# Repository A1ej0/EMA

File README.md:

<div align="center">

</div>  

# <div align="center">EMA - Estación de Monitoreo Automático 🍃</div>  

<div align="right">

</div>  

-  De bajo costo💸  

- Enfoque comunitario 🙆🧑‍🎓🧑‍🌾🧑‍🍳🧑‍🚒  

- De alta tecnologia 🚀🛸  

<br/>  

## Que es?  
EMA nace con el objetivo de brindar una alternativa con un sentido social y un enfoque comunitario a dispositivos tecnológicos de alto coste y complejidad, brindando la oportunidad a la comunidad de participar en temas relacionados a la medición de variables medioambientales para el monitoreo de diferentes factores como lluvias, movimientos del suelo, crecimiento de los ríos y calidad de agua. 🌋🏔️🏞️

Todo esto a muy bajo coste y una construcción modular, con partes de muy fácil obtención para promover la participación de todo el mundo 
🌎  

<br/>  

## Que incluye?  
<div align="center">  

</div>  

El proyecto EMA esta diseñado con un enfoque de codigo abierto y software libre, es por esto que se usaron lenguajes de programacion y aplicativos con este enfoque, para el modulo principal que incluye la placa principal del proyecto (ESP32), se uso micropython, para los sensores externos que requieren un microcontrolador para ser interpretados se uso C++ como codigo de programacion, para la interface web, se hizo uso de Node-red, proyecto de codigo abierto creado por IBM y finalmente Mosquitto como broker de MQTT  

<br/>  

## Características  
- ### Conexión ✨  

📶 Bluetooth, Diseñado para lectura, ajuste y extracción de información desde dispositivos móviles

🥝Wifi, Diseñado para el envió de lecturas de los sensores al servidor del proyecto

📱GPRS, Diseñado para el envió de lectura de sensores mediante una red móvil en caso de ausencia de wifi

📝MicroSD, diseñada para almacenar de forma local lectura de sensores en caso de ausencia de cualquier lectura y como forma de llevar registros

- ### Módulos 🧩  

Los módulos son los sensores que es capaz de leer EMA  

⛈️ Pluviómetro, modulo diseñado para leer los niveles de lluvia en la zona

📏 Distancia, modulo diseñado con ultrasonido para medir distancias de niveles de ríos o similares

🏜️ Temperatura, Modulo diseñado para medir la temperatura medio ambiental

🚄 Aceleración, Modulo diseñado para medir el movimiento de los suelos, montañas, etc

⌛ Reloj, Modulo diseñado para llevar un registro de tiempo del momento de toma de lecturas

💧Calidad de agua, Modulo diseñado para medir el nivel de contaminación de ríos o cuerpos de agua  

- ### Proyección 🚀✨  

Se espera para el futuro la integración de módulos adicionales para lecturas de variables medioambientales diferentes con una variedad mas amplia de sensores, también se pretende el diseño y construcción de un sistema de programación remoto por medio del cual los usuarios podrán cargar el programa en la placa de desarrollo sin requerir ningún programa mas allá de un navegador web 💻  

<br />

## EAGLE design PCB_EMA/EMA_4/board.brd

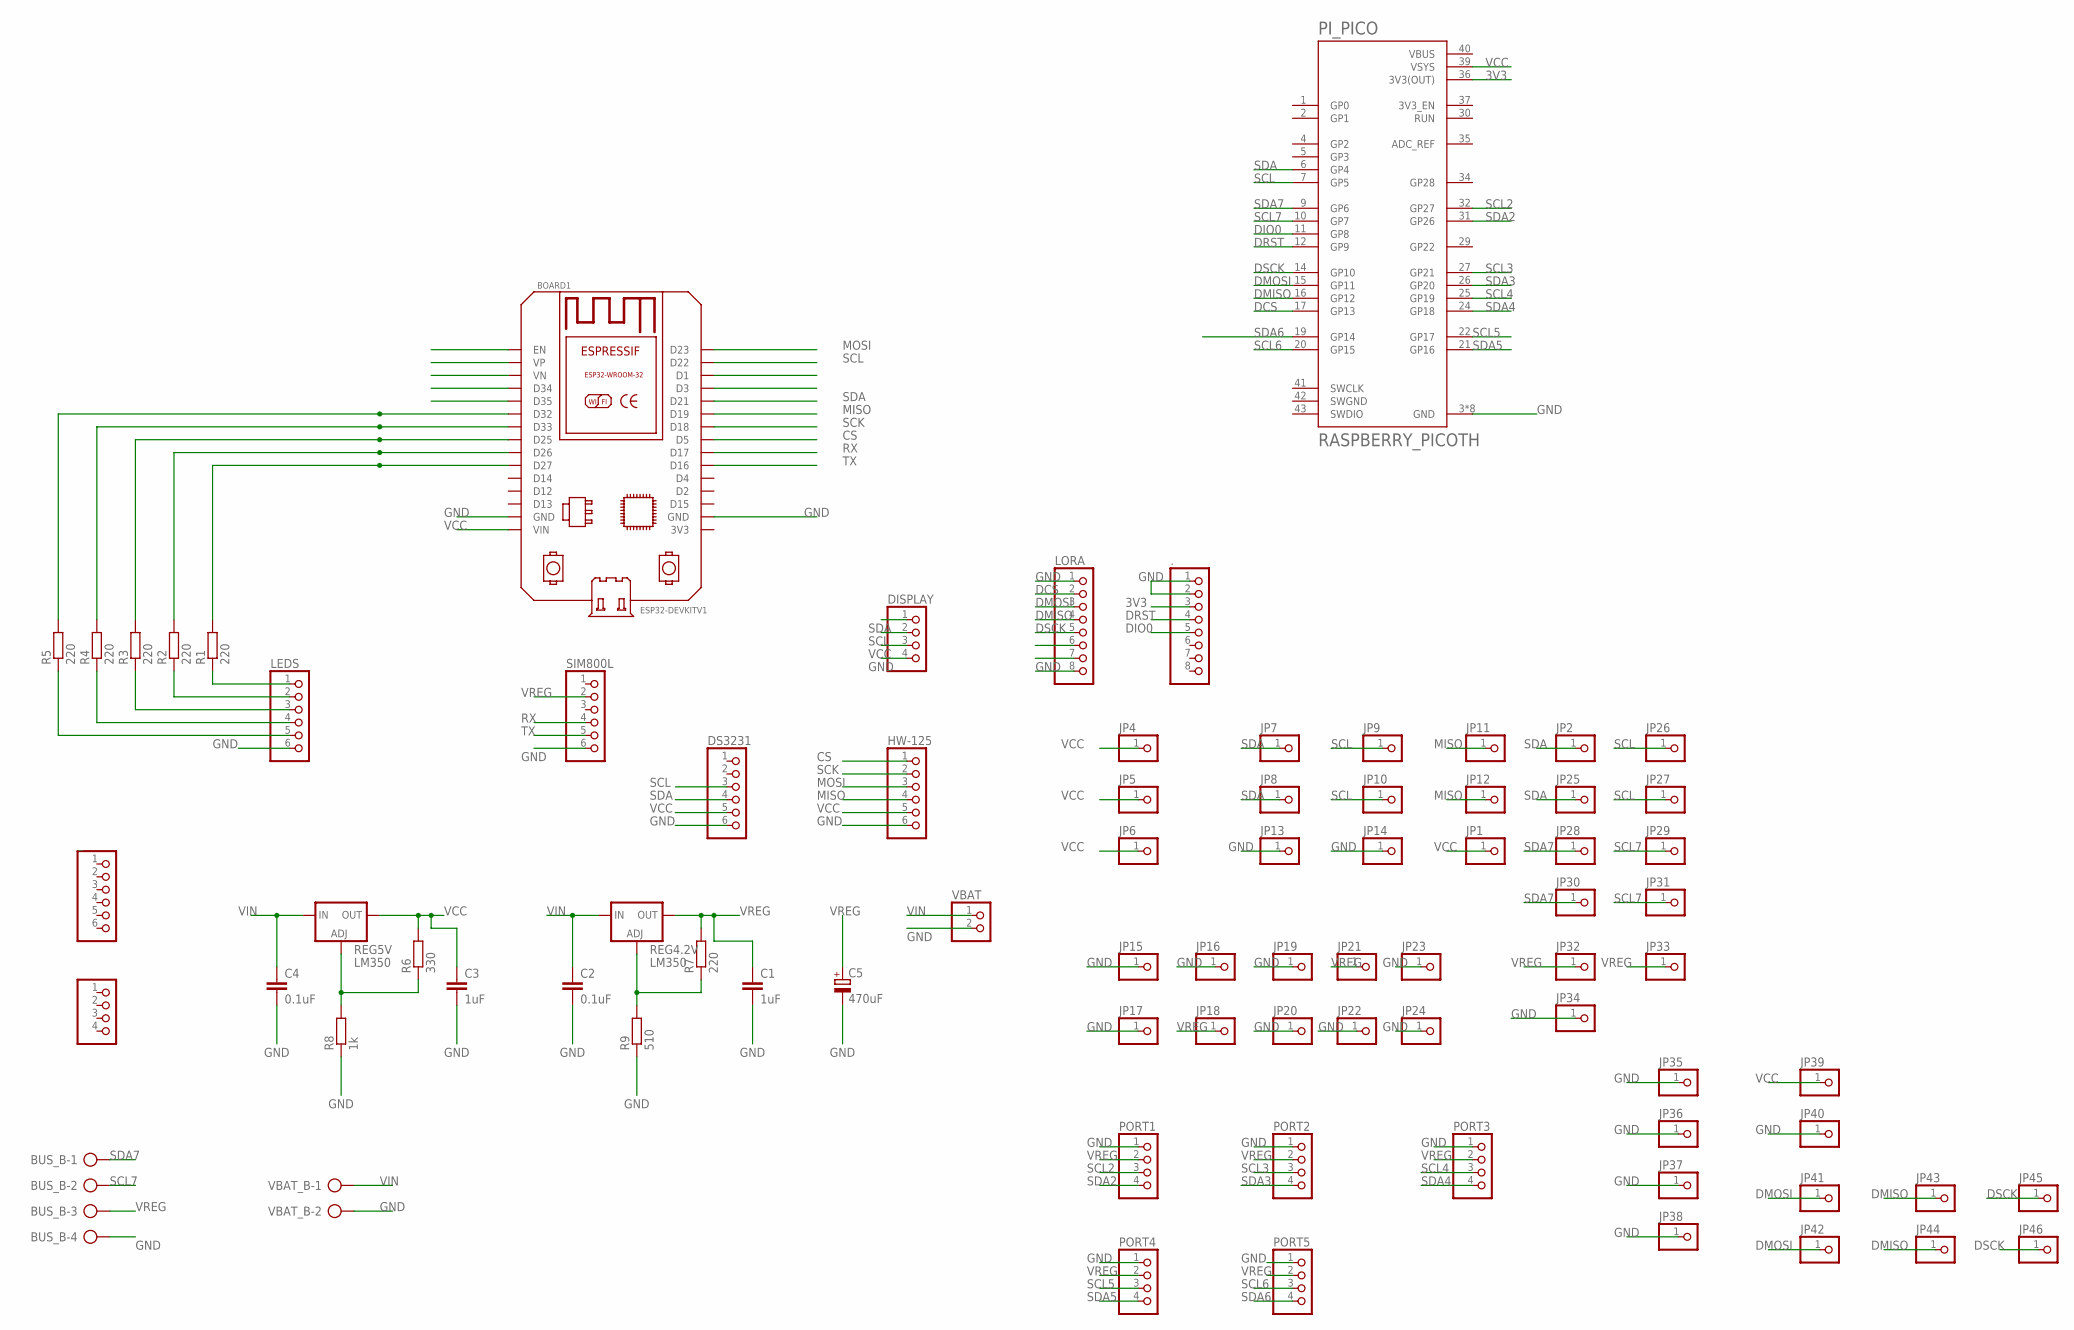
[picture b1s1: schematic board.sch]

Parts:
.: PINHD-1X8; 1X08
BOARD1: ESP32DEVKITV1; ESP32-DEVKITV1
BUS_B: AK500/4-H
C1, C3: 1uF; C2.5-2
C2, C4: 0.1uF; C2.5-2
C5: 470uF; E3,5-8
DISPLAY: PINHD-1X4; 1X04
DS3231: PINHD-1X6; 1X06
HW-125: PINHD-1X6; 1X06
JP1, JP2, JP4, JP5, JP6, JP7, JP8, JP9, JP10, JP11, JP12, JP13, JP14, JP15, JP16, JP17, JP18, JP19, JP20, JP21, JP22, JP23, JP24, JP25, JP26, JP27, JP28, JP29, JP30, JP31, JP32, JP33, JP34, JP35, JP36, JP37, JP38, JP39, JP40, JP41, JP42, JP43, JP44, JP45, JP46: PINHD-1X1; 1X01
JP3: PINHD-1X4; 1X04
LEDS: PINHD-1X6; 1X06
LORA: PINHD-1X8; 1X08
PI_PICO: RASPBERRY_PICOTH; PICO-PKG-TH
PORT1, PORT2, PORT3, PORT4, PORT5: PINHD-1X4; 1X04
R1, R2, R3, R4, R5: 220; R1206
R6: 330; 0204/7
R7: 220; 0204/7
R8: 1k; 0204/7
R9: 510; 0204/7
REG4.2V, REG5V: LM350; 317TS
SIM800L: PINHD-1X6; 1X06
VBAT: PINHD-1X2; 1X02
VBAT_B: AK500/2-H
_: PINHD-1X6; 1X06

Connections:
3V3: ..3, PI_PICO.36 (3V3(OUT))
CS: BOARD1.D5, HW-125.1
DCS: LORA.2, PI_PICO.17 (GP13)
DIO0: ..5, PI_PICO.11 (GP8)
DMISO: JP43.1, JP44.1, LORA.4, PI_PICO.16 (GP12)
DMOSI: JP41.1, JP42.1, LORA.3, PI_PICO.15 (GP11)
DRST: ..4, PI_PICO.12 (GP9)
DSCK: JP45.1, JP46.1, LORA.5, PI_PICO.14 (GP10)
GND: ..1, ..2, BOARD1.GND, BOARD1.GND@1 (GND), BUS_B.4, C1.2, C2.2, C3.2, C4.2, C5.-, DISPLAY.4, DS3231.6, HW-125.6, JP13.1, JP14.1, JP15.1, JP16.1, JP17.1, JP19.1, JP20.1, JP22.1, JP23.1, JP24.1, JP34.1, JP35.1, JP36.1, JP37.1, JP38.1, JP40.1, LEDS.6, LORA.1, LORA.8, PI_PICO.3 (GND), PI_PICO.8 (GND), PI_PICO.13 (GND), PI_PICO.18 (GND), PI_PICO.23 (GND), PI_PICO.28 (GND), PI_PICO.33 (GND), PI_PICO.38 (GND), PORT1.1, PORT2.1, PORT3.1, PORT4.1, PORT5.1, R8.1, R9.1, SIM800L.6, VBAT.2, VBAT_B.2
MISO: BOARD1.D19, HW-125.4, JP11.1, JP12.1
MOSI: BOARD1.D23, HW-125.3
unnamed: BOARD1.D32, R5.2
unnamed: BOARD1.D33, R4.2
unnamed: BOARD1.D25, R3.2
unnamed: BOARD1.D26, R2.2
unnamed: BOARD1.D27, R1.2
unnamed: LEDS.1, R1.1
unnamed: LEDS.2, R2.1
unnamed: LEDS.3, R3.1
unnamed: LEDS.4, R4.1
unnamed: LEDS.5, R5.1
unnamed: R6.1, R8.2, REG5V.1 (ADJ)
unnamed: R7.1, R9.2, REG4.2V.1 (ADJ)
RX: BOARD1.D17, SIM800L.4
SCK: BOARD1.D18, HW-125.2
SCL: BOARD1.D22, DISPLAY.2, DS3231.3, JP9.1, JP10.1, JP26.1, JP27.1, PI_PICO.7 (GP5)
SCL2: PI_PICO.32 (GP27), PORT1.3
SCL3: PI_PICO.27 (GP21), PORT2.3
SCL4: PI_PICO.25 (GP19), PORT3.3
SCL5: PI_PICO.22 (GP17), PORT4.3
SCL6: PI_PICO.20 (GP15), PORT5.3
SCL7: BUS_B.2, JP29.1, JP31.1, PI_PICO.10 (GP7)
SDA: BOARD1.D21, DISPLAY.1, DS3231.4, JP2.1, JP7.1, JP8.1, JP25.1, PI_PICO.6 (GP4)
SDA2: PI_PICO.31 (GP26), PORT1.4
SDA3: PI_PICO.26 (GP20), PORT2.4
SDA4: PI_PICO.24 (GP18), PORT3.4
SDA5: PI_PICO.21 (GP16), PORT4.4
SDA6: PI_PICO.19 (GP14), PORT5.4
SDA7: BUS_B.1, JP28.1, JP30.1, PI_PICO.9 (GP6)
SWGND: PI_PICO.42 (SWGND)
TX: BOARD1.D16, SIM800L.5
VBUS: PI_PICO.40 (VBUS)
VCC: BOARD1.VIN, C3.1, DISPLAY.3, DS3231.5, HW-125.5, JP1.1, JP4.1, JP5.1, JP6.1, JP39.1, PI_PICO.39 (VSYS), R6.2, REG5V.2 (OUT)
VIN: C2.1, C4.1, REG4.2V.3 (IN), REG5V.3 (IN), VBAT.1, VBAT_B.1
VREG: BUS_B.3, C1.1, C5.+, JP18.1, JP21.1, JP32.1, JP33.1, PORT1.2, PORT2.2, PORT3.2, PORT4.2, PORT5.2, R7.2, REG4.2V.2 (OUT), SIM800L.2

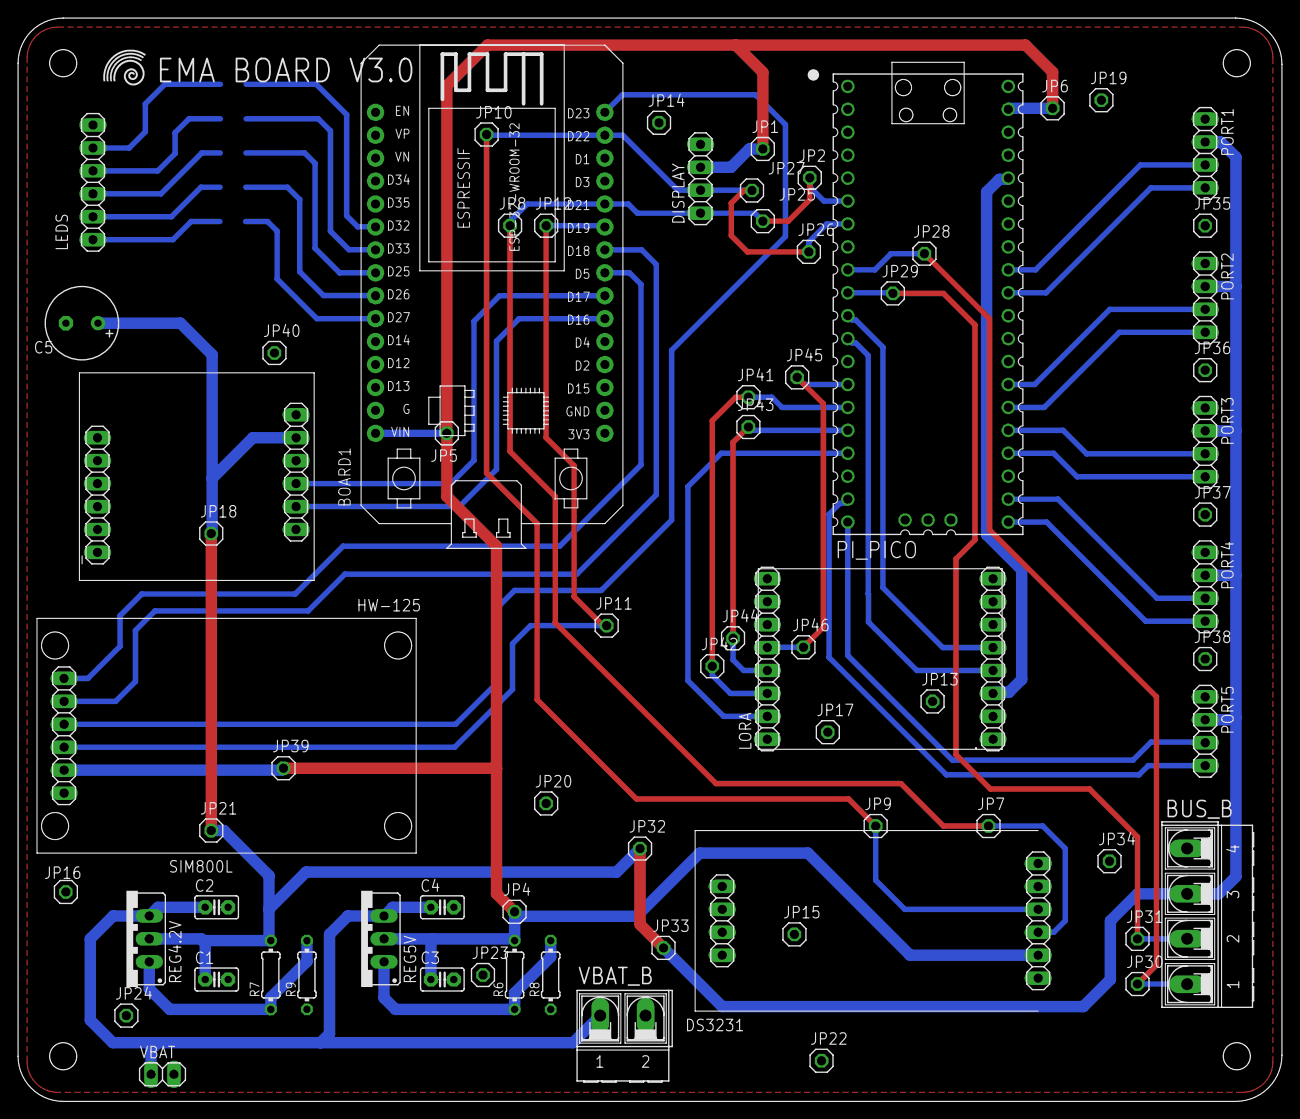
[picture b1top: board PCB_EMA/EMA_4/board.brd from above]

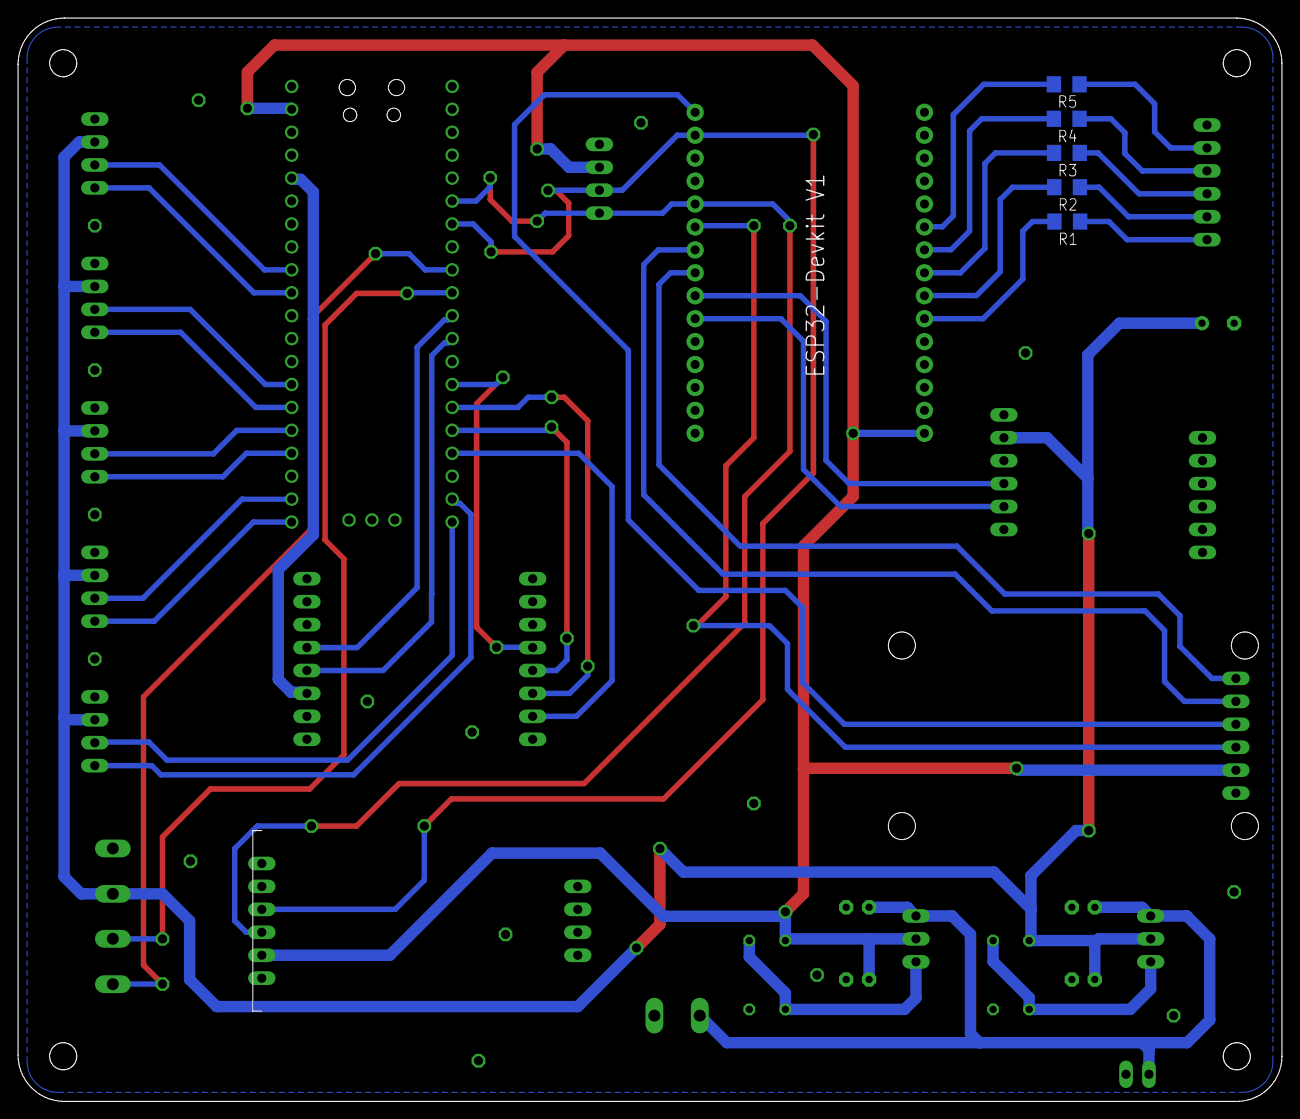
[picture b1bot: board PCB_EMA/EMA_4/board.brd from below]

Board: 2 copper layers, 140.0 x 120.0 mm, 80 parts (5 on the bottom side), 43 nets.

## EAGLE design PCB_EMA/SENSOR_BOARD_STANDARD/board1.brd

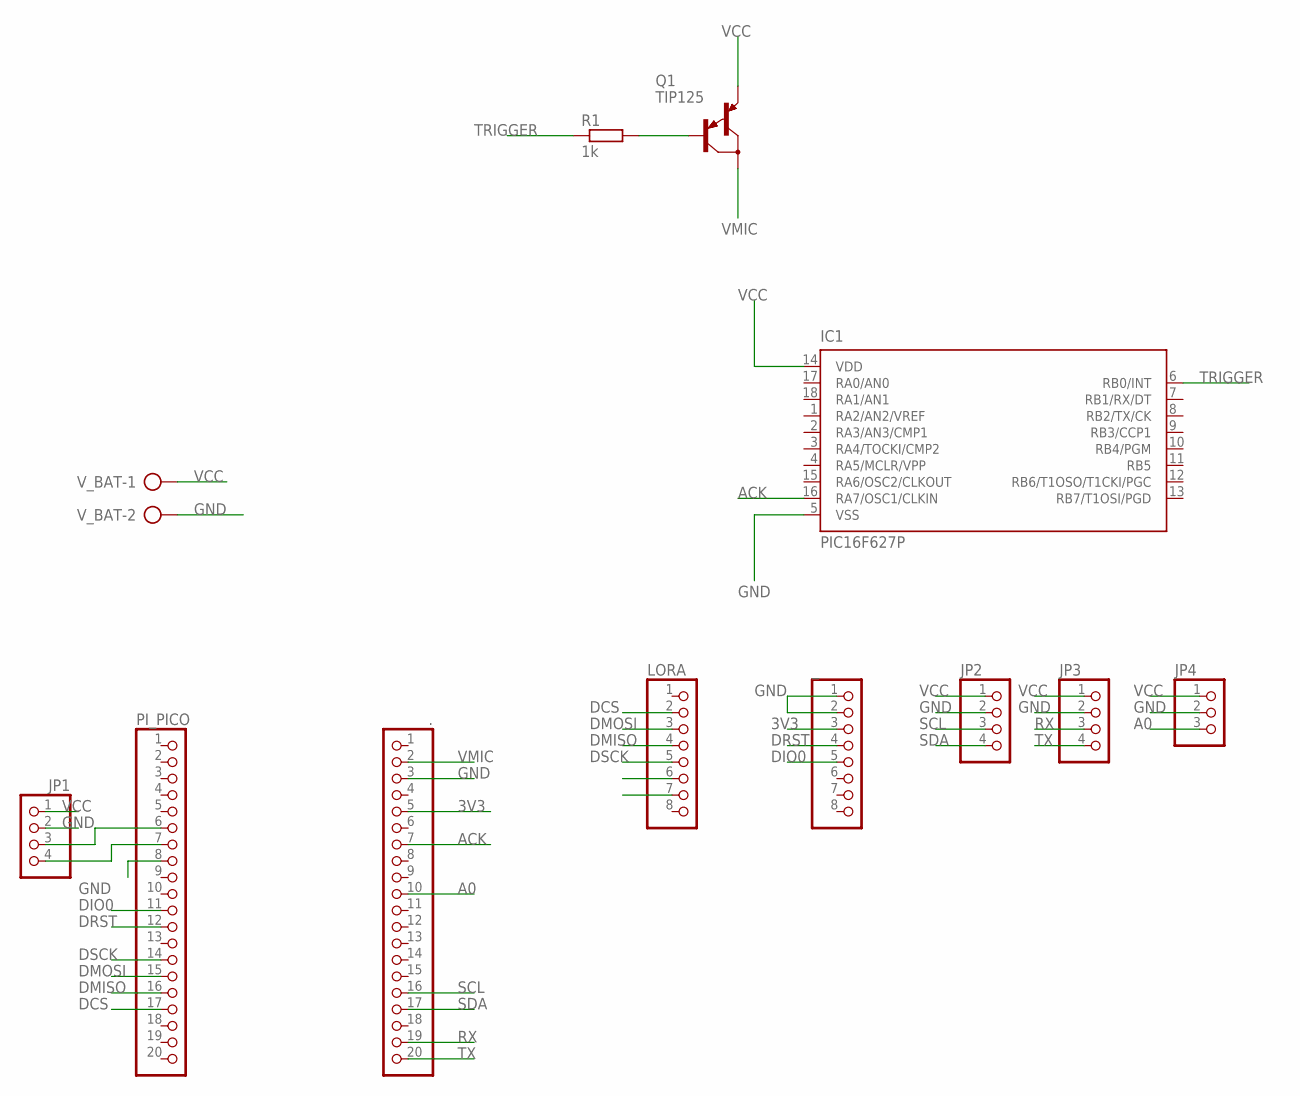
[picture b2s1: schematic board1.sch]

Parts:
.: PINHD-1X20; 1X20
IC1: PIC16F627P; DIL18
JP1, JP2, JP3: PINHD-1X4; 1X04
JP4: PINHD-1X3; 1X03
LORA: PINHD-1X8; 1X08
PI_PICO: PINHD-1X20; 1X20
Q1: TIP125; TO220
R1: 1k; 0411/15
V_BAT: AK500/2-H
_: PINHD-1X8; 1X08

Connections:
3V3: ..5, _.3
A0: ..10, JP4.3
ACK: ..7, IC1.16 (RA7/OSC1/CLKIN)
DCS: LORA.2, PI_PICO.17
DIO0: PI_PICO.11, _.5
DMISO: LORA.4, PI_PICO.16
DMOSI: LORA.3, PI_PICO.15
DRST: PI_PICO.12, _.4
DSCK: LORA.5, PI_PICO.14
GND: ..3, IC1.5 (VSS), JP1.2, JP2.2, JP3.2, JP4.2, PI_PICO.8, V_BAT.2, _.1, _.2
unnamed: JP1.4, PI_PICO.7
unnamed: JP1.3, PI_PICO.6
unnamed: Q1.1 (B), R1.2
RX: ..19, JP3.3
SCL: ..16, JP2.3
SDA: ..17, JP2.4
TRIGGER: IC1.6 (RB0/INT), R1.1
TX: ..20, JP3.4
VCC: IC1.14 (VDD), JP1.1, JP2.1, JP3.1, JP4.1, Q1.3 (E), V_BAT.1
VMIC: ..2, Q1.2 (C)

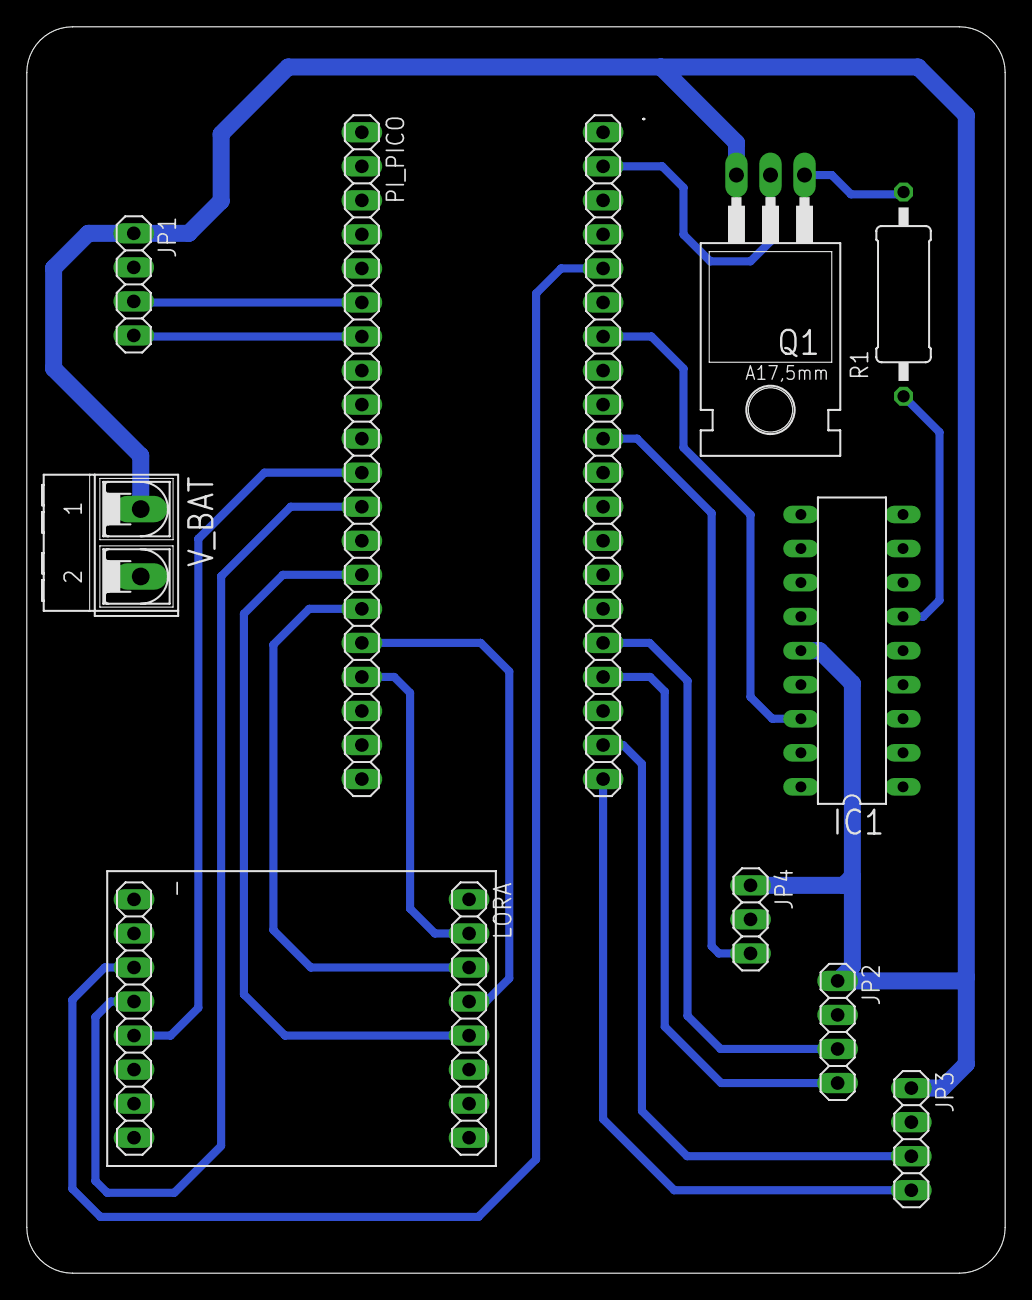
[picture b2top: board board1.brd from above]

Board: 2 copper layers, 73.0 x 93.0 mm, 12 parts (0 on the bottom side), 20 nets.

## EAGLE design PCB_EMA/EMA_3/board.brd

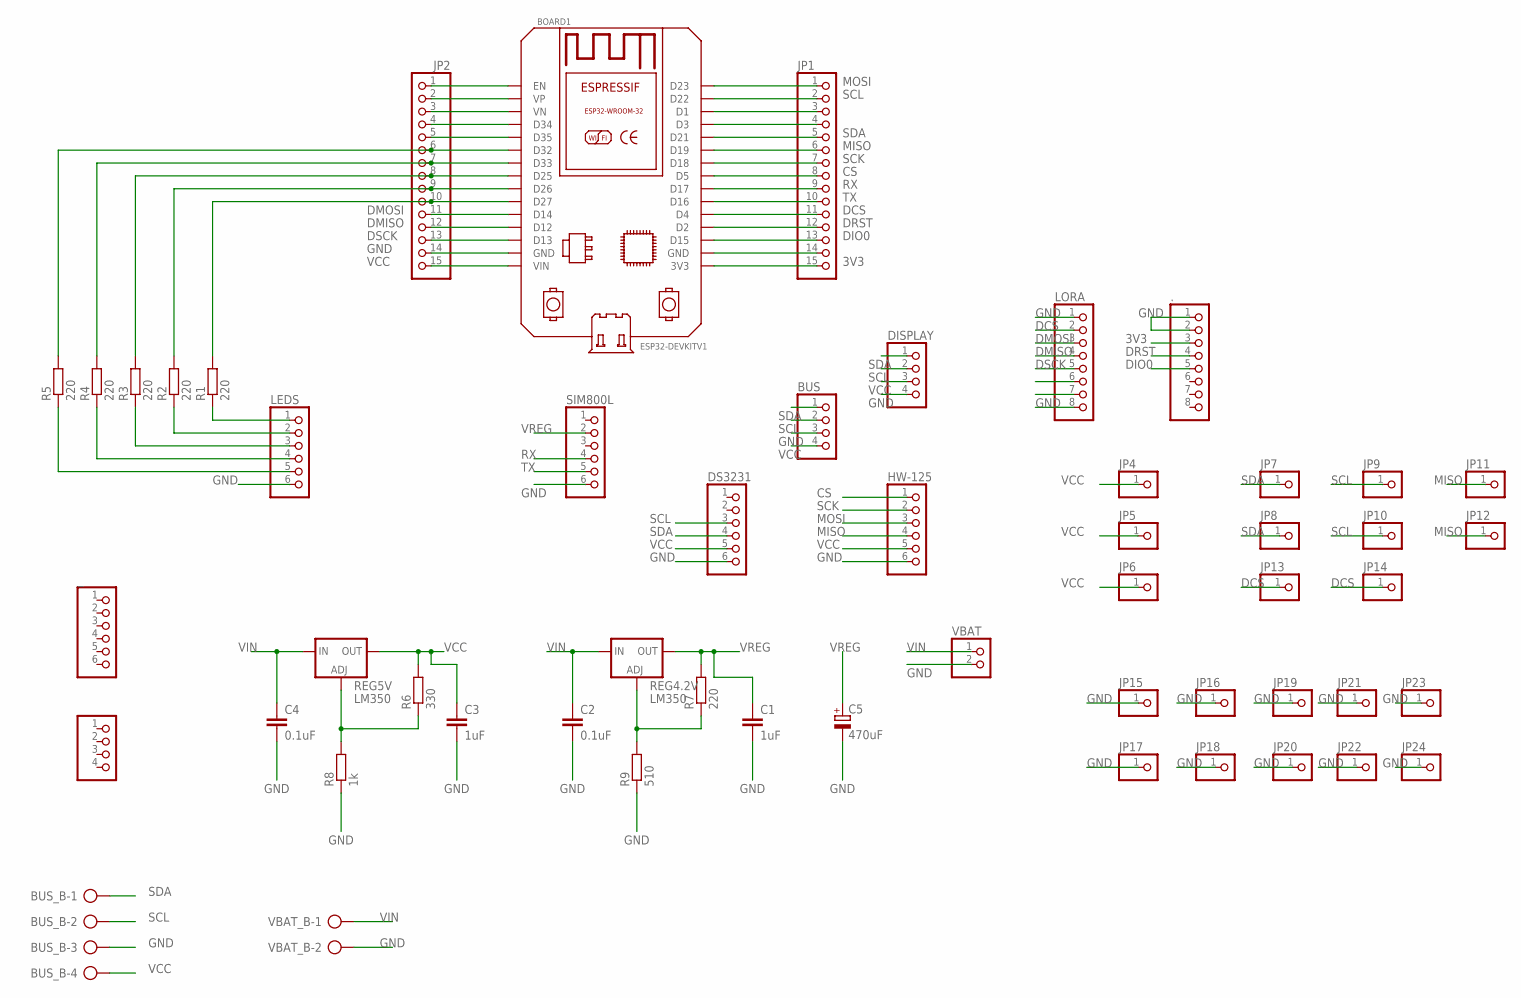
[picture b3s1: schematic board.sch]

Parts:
.: PINHD-1X8; 1X08
BOARD1: ESP32DEVKITV1; ESP32-DEVKITV1
BUS: PINHD-1X4; 1X04
BUS_B: AK500/4-H
C1, C3: 1uF; C2.5-2
C2, C4: 0.1uF; C2.5-2
C5: 470uF; E3,5-8
DISPLAY: PINHD-1X4; 1X04
DS3231: PINHD-1X6; 1X06
HW-125: PINHD-1X6; 1X06
JP1, JP2: PINHD-1X15; 1X15
JP3: PINHD-1X4; 1X04
JP4, JP5, JP6, JP7, JP8, JP9, JP10, JP11, JP12, JP13, JP14, JP15, JP16, JP17, JP18, JP19, JP20, JP21, JP22, JP23, JP24: PINHD-1X1; 1X01
LEDS: PINHD-1X6; 1X06
LORA: PINHD-1X8; 1X08
R1, R2, R3, R4, R5: 220; R1206
R6: 330; 0204/7
R7: 220; 0204/7
R8: 1k; 0204/7
R9: 510; 0204/7
REG4.2V, REG5V: LM350; 317TS
SIM800L: PINHD-1X6; 1X06
VBAT: PINHD-1X2; 1X02
VBAT_B: AK500/2-H
_: PINHD-1X6; 1X06

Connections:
3V3: ..3, BOARD1.3V3, JP1.15
CS: BOARD1.D5, HW-125.1, JP1.8
DCS: BOARD1.D4, JP1.11, JP13.1, JP14.1, LORA.2
DIO0: ..5, BOARD1.D15, JP1.13
DMISO: BOARD1.D12, JP2.12, LORA.4
DMOSI: BOARD1.D14, JP2.11, LORA.3
DRST: ..4, BOARD1.D2, JP1.12
DSCK: BOARD1.D13, JP2.13, LORA.5
GND: ..1, ..2, BOARD1.GND, BUS.3, BUS_B.3, C1.2, C2.2, C3.2, C4.2, C5.-, DISPLAY.4, DS3231.6, HW-125.6, JP2.14, JP15.1, JP16.1, JP17.1, JP18.1, JP19.1, JP20.1, JP21.1, JP22.1, JP23.1, JP24.1, LEDS.6, LORA.1, LORA.8, R8.1, R9.1, SIM800L.6, VBAT.2, VBAT_B.2
MISO: BOARD1.D19, HW-125.4, JP1.6, JP11.1, JP12.1
MOSI: BOARD1.D23, HW-125.3, JP1.1
unnamed: BOARD1.EN, JP2.1
unnamed: BOARD1.VP, JP2.2
unnamed: BOARD1.VN, JP2.3
unnamed: BOARD1.D34, JP2.4
unnamed: BOARD1.D35, JP2.5
unnamed: BOARD1.D32, JP2.6, R5.2
unnamed: BOARD1.D33, JP2.7, R4.2
unnamed: BOARD1.D25, JP2.8, R3.2
unnamed: BOARD1.D26, JP2.9, R2.2
unnamed: BOARD1.D27, JP2.10, R1.2
unnamed: LEDS.1, R1.1
unnamed: LEDS.2, R2.1
unnamed: LEDS.3, R3.1
unnamed: LEDS.4, R4.1
unnamed: LEDS.5, R5.1
unnamed: BOARD1.D1, JP1.3
unnamed: BOARD1.D3, JP1.4
unnamed: BOARD1.GND@1 (GND), JP1.14
unnamed: R6.1, R8.2, REG5V.1 (ADJ)
unnamed: R7.1, R9.2, REG4.2V.1 (ADJ)
RX: BOARD1.D17, JP1.9, SIM800L.4
SCK: BOARD1.D18, HW-125.2, JP1.7
SCL: BOARD1.D22, BUS.2, BUS_B.2, DISPLAY.2, DS3231.3, JP1.2, JP9.1, JP10.1
SDA: BOARD1.D21, BUS.1, BUS_B.1, DISPLAY.1, DS3231.4, JP1.5, JP7.1, JP8.1
TX: BOARD1.D16, JP1.10, SIM800L.5
VCC: BOARD1.VIN, BUS.4, BUS_B.4, C3.1, DISPLAY.3, DS3231.5, HW-125.5, JP2.15, JP4.1, JP5.1, JP6.1, R6.2, REG5V.2 (OUT)
VIN: C2.1, C4.1, REG4.2V.3 (IN), REG5V.3 (IN), VBAT.1, VBAT_B.1
VREG: C1.1, C5.+, R7.2, REG4.2V.2 (OUT), SIM800L.2

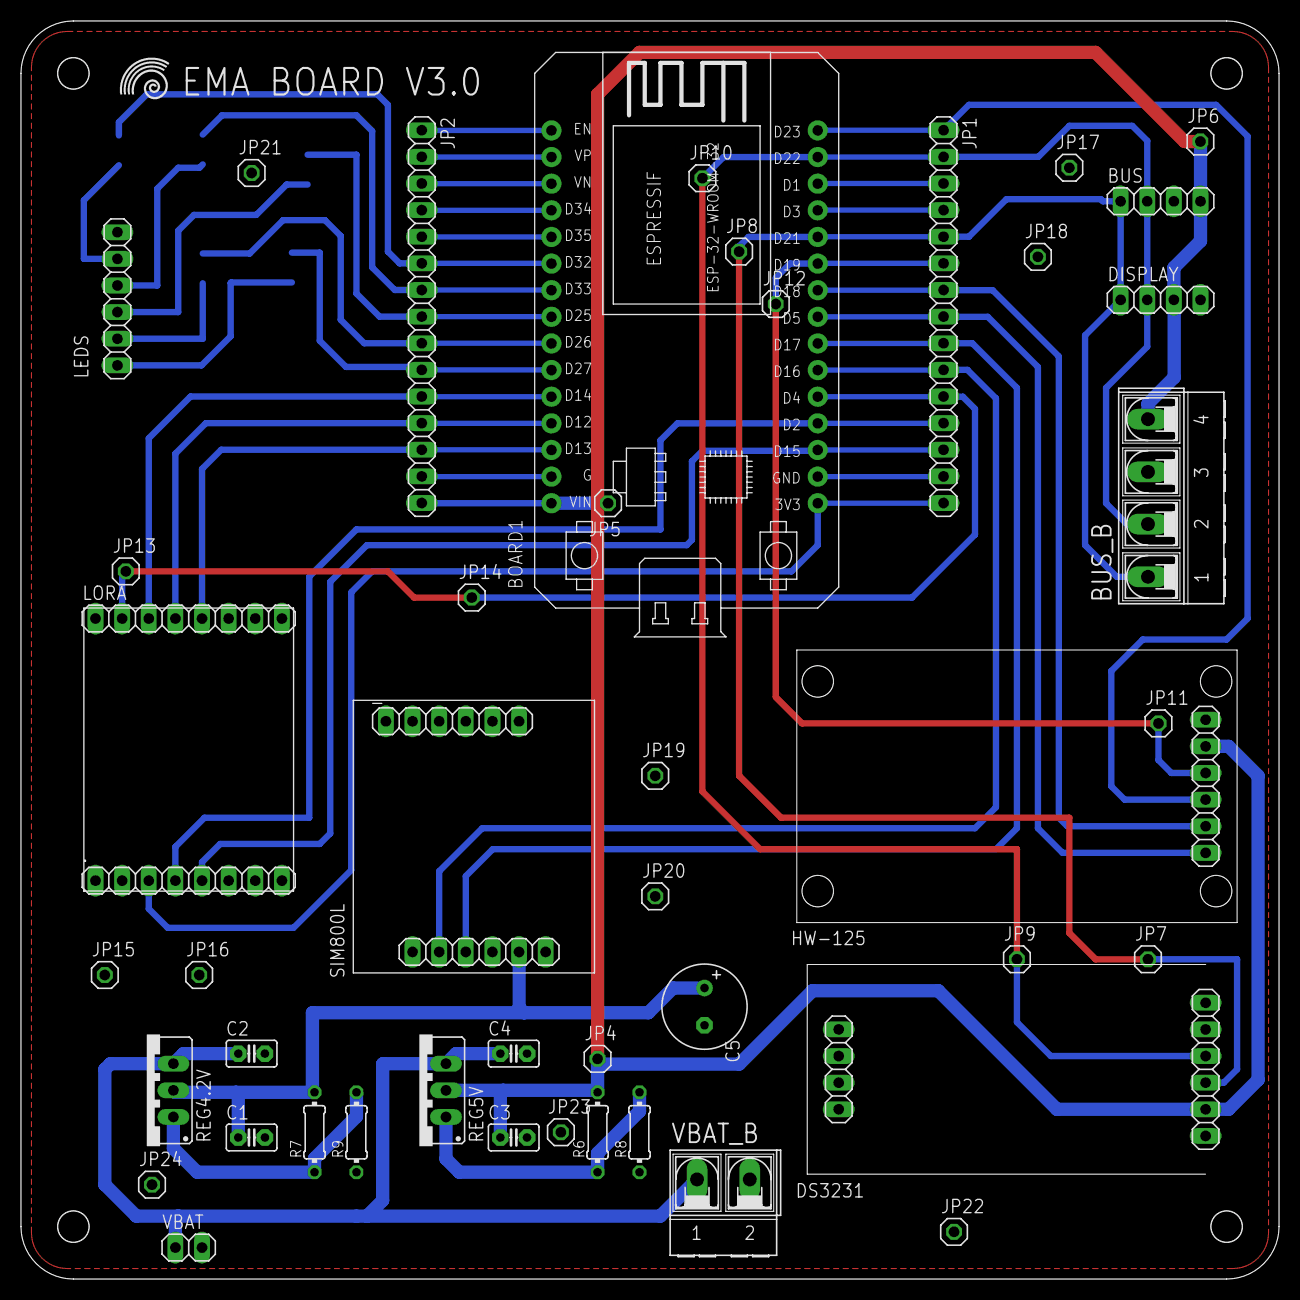
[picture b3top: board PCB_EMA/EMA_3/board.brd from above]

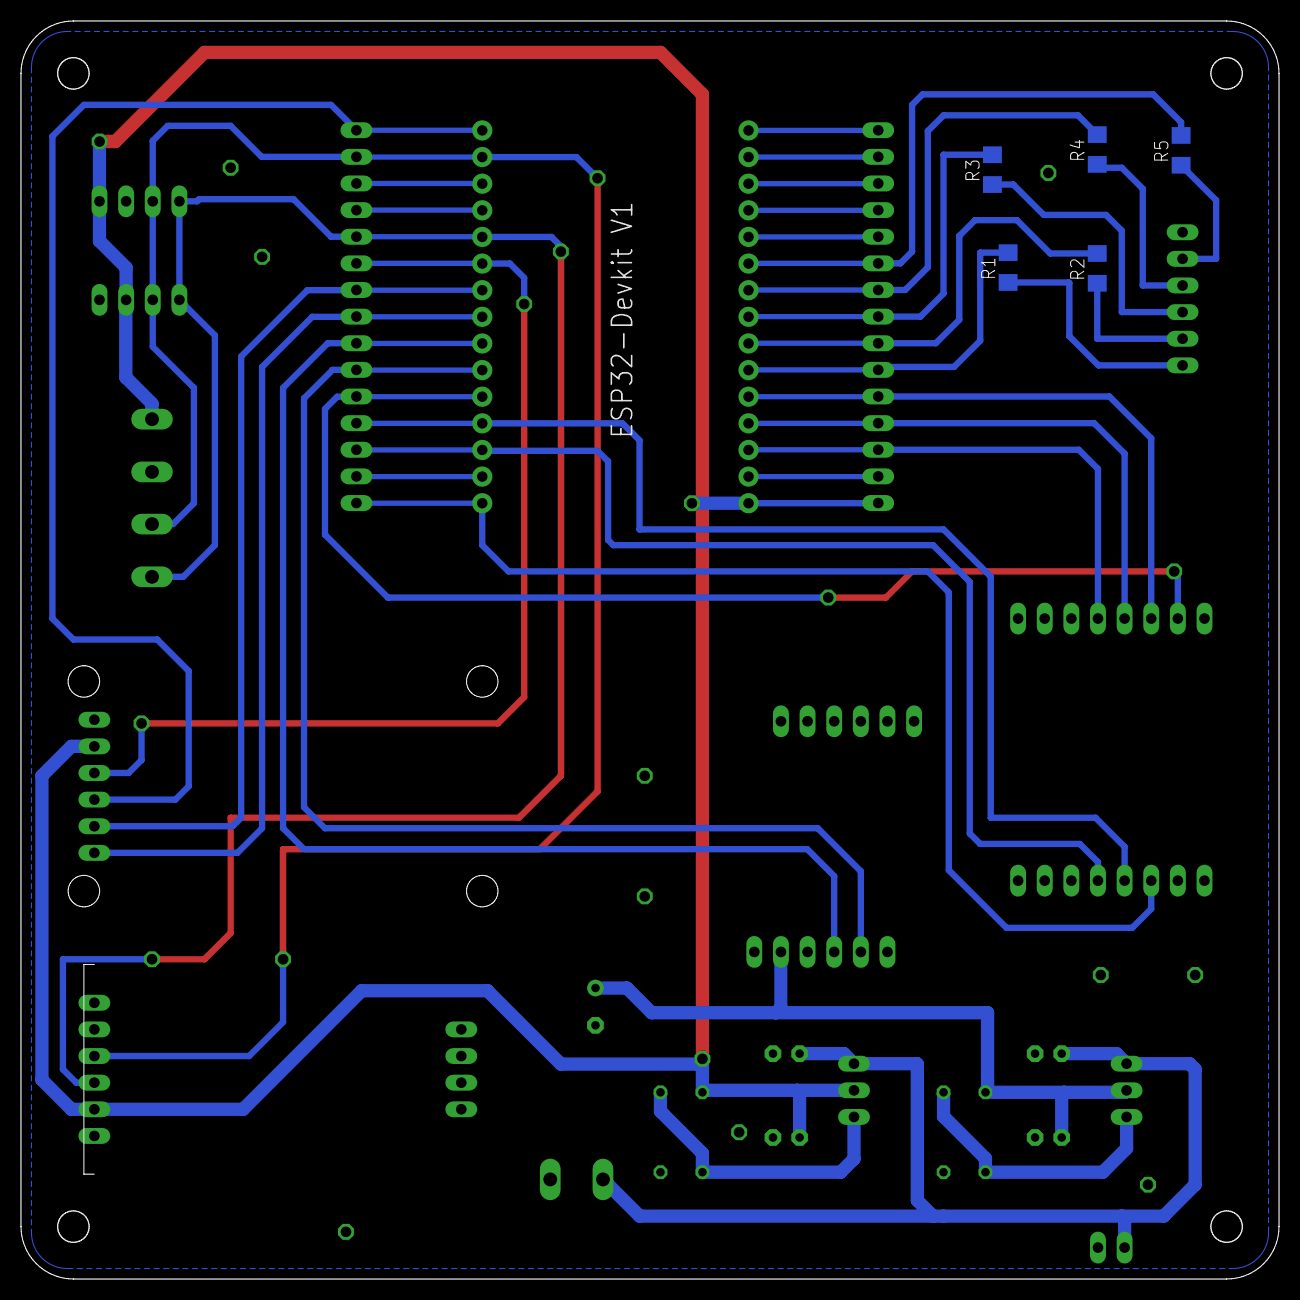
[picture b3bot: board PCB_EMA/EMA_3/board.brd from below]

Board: 2 copper layers, 120.0 x 120.0 mm, 53 parts (5 on the bottom side), 39 nets.

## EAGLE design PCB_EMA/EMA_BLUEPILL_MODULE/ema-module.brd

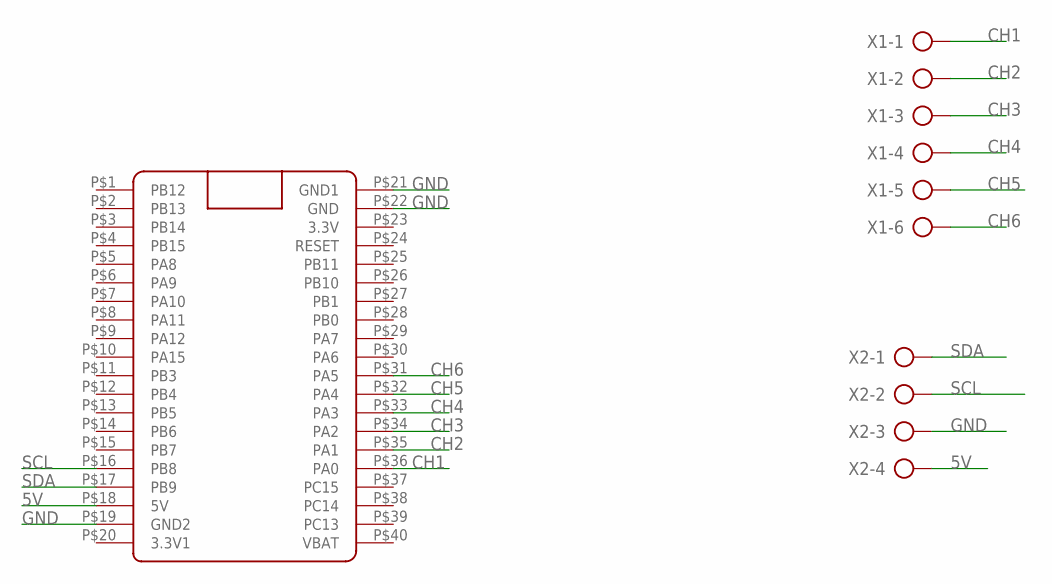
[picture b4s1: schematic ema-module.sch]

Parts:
U$1: BLUE_PILL
X1: AK500/6-H
X2: AK500/4-H

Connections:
5V: U$1.P$18 (5V), X2.4
CH1: U$1.P$36 (PA0), X1.1
CH2: U$1.P$35 (PA1), X1.2
CH3: U$1.P$34 (PA2), X1.3
CH4: U$1.P$33 (PA3), X1.4
CH5: U$1.P$32 (PA4), X1.5
CH6: U$1.P$31 (PA5), X1.6
GND: U$1.P$19 (GND2), U$1.P$21 (GND1), U$1.P$22 (GND), X2.3
SCL: U$1.P$16 (PB8), X2.2
SDA: U$1.P$17 (PB9), X2.1

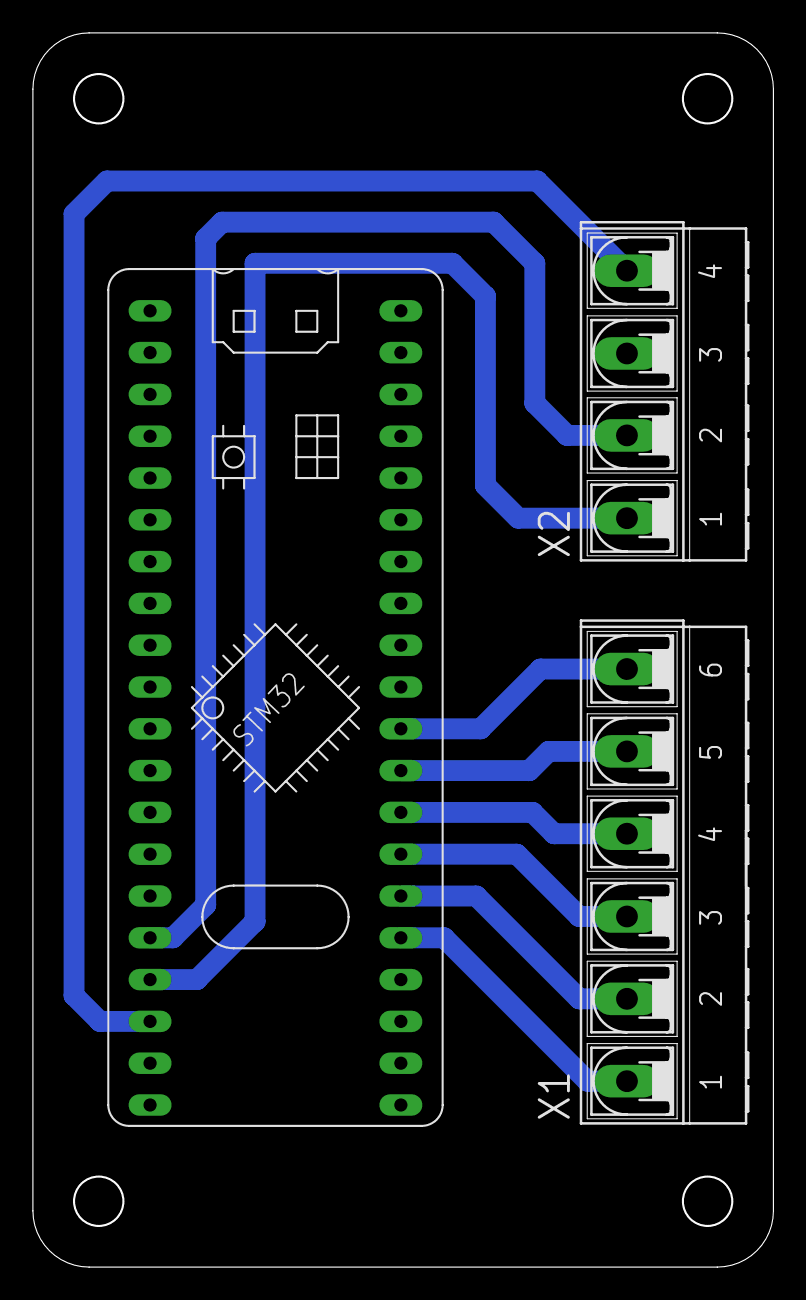
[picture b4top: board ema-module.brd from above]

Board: 2 copper layers, 45.0 x 75.0 mm, 3 parts (0 on the bottom side), 10 nets.

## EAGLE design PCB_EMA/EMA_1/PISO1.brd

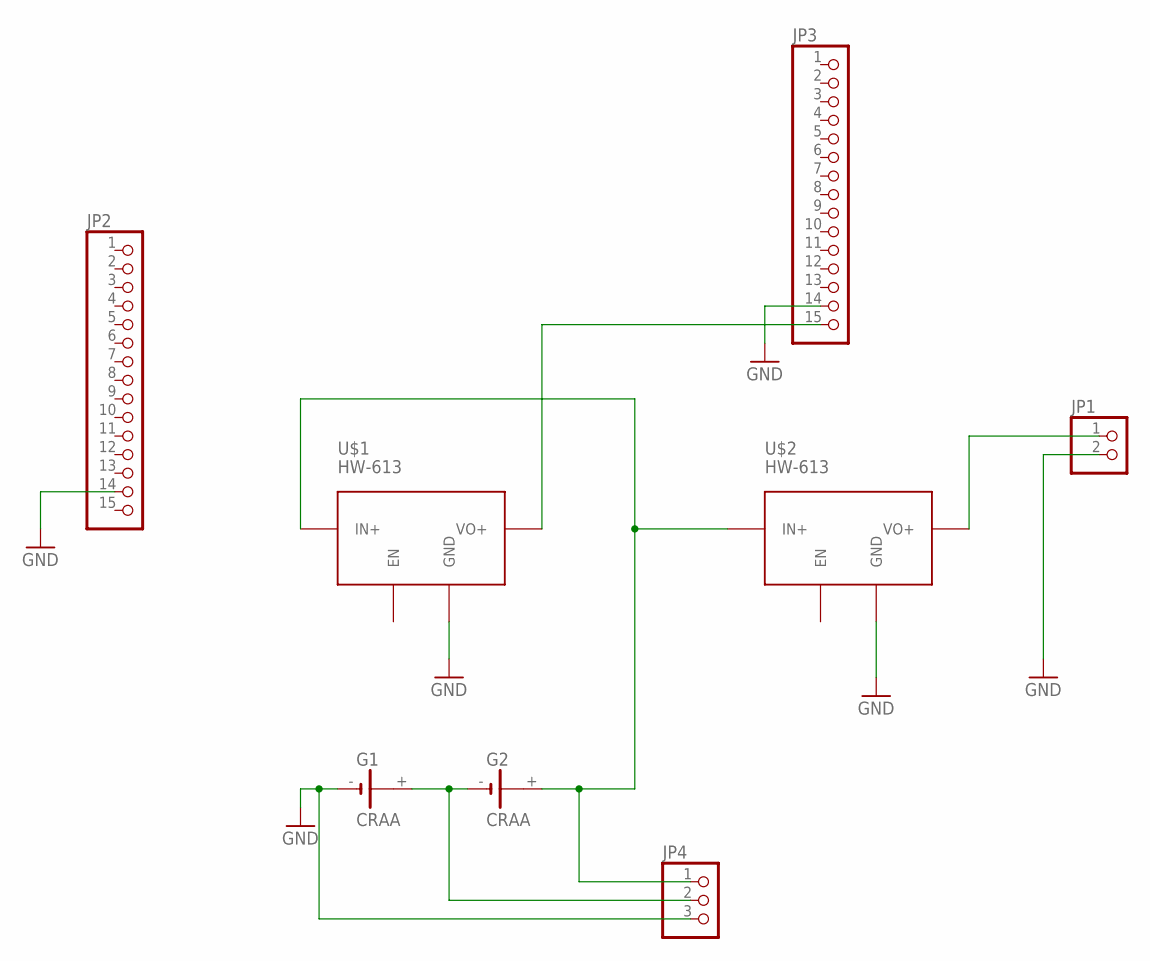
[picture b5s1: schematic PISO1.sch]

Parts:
G1, G2: CRAA
JP1: PINHD-1X2/90; 1X02/90
JP2, JP3: PINHD-1X15; 1X15
JP4: PINHD-1X3/90; 1X03/90
U$1, U$2: HW-613

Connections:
GND: G1.-, JP1.2, JP2.14, JP3.14, JP4.3, U$1.GND, U$2.GND
unnamed: G1.+, G2.-, JP4.2
unnamed: G2.+, JP4.1, U$1.IN+, U$2.IN+
unnamed: JP1.1, U$2.VO+
unnamed: JP3.15, U$1.VO+
